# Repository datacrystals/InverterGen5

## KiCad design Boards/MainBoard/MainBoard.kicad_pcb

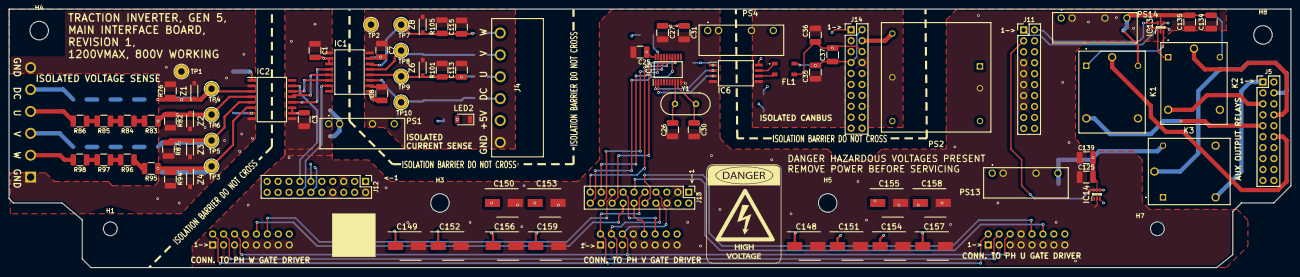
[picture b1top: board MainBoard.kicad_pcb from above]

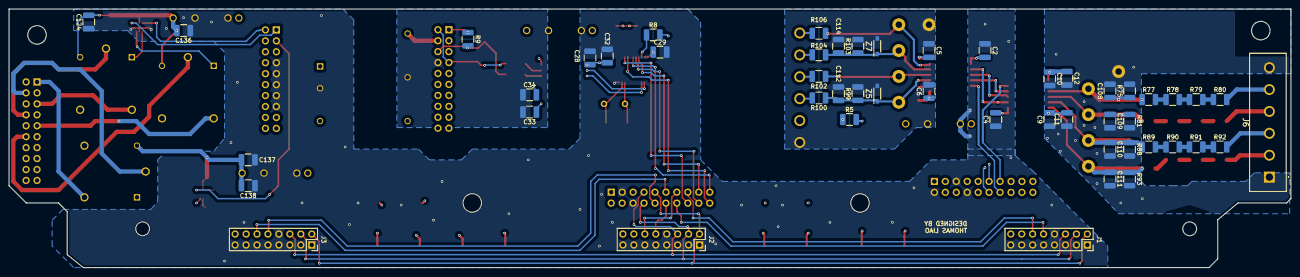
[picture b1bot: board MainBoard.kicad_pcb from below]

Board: 6 copper layers, 297.5 x 60.0 mm, 139 parts (50 on the bottom side), 85 nets.

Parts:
C1, C3, C5, C6, C9, C10, C25, C31, C32, C34: 100nF; C_1210_3225Metric_Pad1.33x2.70mm_HandSolder
C2, C4, C7, C8, C11, C12: 1uF; C_1210_3225Metric_Pad1.33x2.70mm_HandSolder
C26, C30, C35, C36, C37: 22pF; C_1210_3225Metric_Pad1.33x2.70mm_HandSolder
C27, C28, C29, C33, C124, C125, C134, C135, C136, C137, C138, C139: 10uF; C_1210_3225Metric_Pad1.33x2.70mm_HandSolder
C108, C109, C110, C111, C112, C113, C114, C115: 10nF; C_1210_3225Metric_Pad1.33x2.70mm_HandSolder
C148, C149, C150, C151, C152, C153, C154, C155, C156, C157, C158, C159: UCM1H101MCL1GS; CAPAE660X800N
FL1: ACT45B-101-2P-TL003; ACT45B1012PTL003
H1, H7: MountingHole; MountingHole_3.2mm_M3
H3, H4, H5, H8: MountingHole; MountingHole_4.3mm_M4
IC1, IC2: MAX22530AWE+; SOIC127P1032X265-16N
IC5: MCP2515-e_ST; SOP65P640X120-20N
IC6: ISO1042BDWVR; SOIC127P1150X280-8N
IC13, IC14: DRDNB21D-7; SOT65P210X110-6N
J1, J2, J3: Conn_02x08_Counter_Clockwise; PinSocket_2x08_P2.54mm_Vertical
J4: TBP01R1-508-06BE; TBP01R150806BE
J5, J11, J12, J13, J14: Conn_02x10_Counter_Clockwise; PinHeader_2x10_P2.54mm_Vertical
J6: TBP01R2-508-06BE; TBP01R250806BE
K1, K2, K3: AWHSH105D00G
LED2: LTST-C230CKT; LEDC3216X120N
PS1, PS4, PS13, PS14: RKE-1205S_H; RKE1205SH
PS2: REC10K-2424DAW_H2; REC10K-AW
R5, R76, R82, R88, R94, R99, R101, R103, R105: 1k; R_1210_3225Metric_Pad1.30x2.65mm_HandSolder
R8: 4.7k; R_1210_3225Metric_Pad1.30x2.65mm_HandSolder
R9: 120; R_1210_3225Metric_Pad1.30x2.65mm_HandSolder
R75, R81, R87, R93: 2k; R_1210_3225Metric_Pad1.30x2.65mm_HandSolder
R77, R78, R79, R80, R83, R84, R85, R86, R89, R90, R91, R92, R95, R96, R97, R98: 250k; R_1210_3225Metric_Pad1.30x2.65mm_HandSolder
R100, R102, R104, R106: 5k; R_1210_3225Metric_Pad1.30x2.65mm_HandSolder
TP1, TP2, TP3, TP4, TP5, TP6, TP7, TP8, TP9, TP10: TestPoint; TestPoint_Loop_D2.54mm_Drill1.5mm_Beaded
Y1: 8MHz; Crystal_HC49-4H_Vertical
Z1, Z2, Z3, Z4, Z5, Z6, Z7, Z8: SZMMSZ4678T1G; SOD3716X135N

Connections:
/+3.3V_A: C1.2, C2.2, C3.2, C4.2, C25.1, C28.2, C29.1, C32.1, C148.1 (+), C149.1 (+), C150.1 (+), C151.1 (+), IC1.10 (VDDPL), IC1.11 (VDDL), IC2.10 (VDDPL), IC2.11 (VDDL), IC5.20 (VDD), IC6.1 (VCC1), J1.14, J2.14, J3.14, J12.1, J12.4, J12.7, J13.1, J13.4, R8.2
/+5V_Y: J4.5, PS1.7 (+VOUT), R5.2
/+12V_A: C27.1, C31.1, C152.1 (+), C153.1 (+), C154.1 (+), C155.1 (+), C156.1 (+), C157.1 (+), C158.1 (+), C159.1 (+), J1.16, J2.16, J3.16, J11.6, J11.8, J11.10, J11.12, J11.14, J12.3, J12.6, J12.9, J13.2, J13.5, PS1.1 (+VIN), PS2.1 (+VIN), PS4.1 (+VIN), PS13.1 (+VIN), PS14.1 (+VIN)
/ADC_1/ADC2_5VFILTER_1/OUT: C112.1, IC1.3 (AIN1), R99.1, R100.1, TP10.1, Z5.1 (K)
/ADC_1/ADC2_5VFILTER_2/OUT: C113.1, IC1.4 (AIN2), R101.1, R102.1, TP9.1, Z6.1 (K)
/ADC_1/ADC2_5VFILTER_3/OUT: C114.1, IC1.5 (AIN3), R103.1, R104.1, TP8.1, Z7.1 (K)
/ADC_1/ADC2_5VFILTER_4/OUT: C115.1, IC1.6 (AIN4), R105.1, R106.1, TP7.1, Z8.1 (K)
/ADC_1/VoltageSenseInputStage1/LV_OUT: C109.1, IC2.4 (AIN2), R81.1, R82.1, R83.1, TP6.1, Z2.1 (K)
/ADC_1/VoltageSenseInputStage2/LV_OUT: C110.1, IC2.5 (AIN3), R87.1, R88.1, R89.1, TP5.1, Z3.1 (K)
/ADC_1/VoltageSenseInputStage3/LV_OUT: C111.1, IC2.6 (AIN4), R93.1, R94.1, R95.1, TP3.1, Z4.1 (K)
/ADC_1/VoltageSenseInputStage/LV_OUT: C108.1, IC2.3 (AIN1), R75.1, R76.1, R77.1, TP4.1, Z1.1 (K)
/CAN_5V_OUT: C33.1, C34.2, IC6.8 (VCC2), PS4.7 (+VOUT)
/CAN_24V_OUT: J14.4, PS2.6 (+VOUT)
/CAN_GND: C33.2, C34.1, C35.1, C36.2, IC6.5 (GND2), J14.8, PS2.5 (COM), PS4.5 (-VOUT)
/CAN_HIGH: C35.2, C37.1, FL1.4, J14.2, J14.7
/CAN_JUMPER_B: J14.1, R9.1
/CAN_LOW: C36.1, C37.2, FL1.3, J14.6, R9.2
/DC_LINK_VSENSE_U: J6.5, R80.2
/FAULT: J1.2, J2.2, J3.2, J13.9
/GND_A: C1.1, C2.1, C3.1, C4.1, C25.2, C26.2, C27.2, C28.1, C29.2, C30.2, C31.2, C32.2, C124.1, C125.1, C134.1, C135.1, C136.1, C137.1, C138.1, C139.1, C148.2 (-), C149.2 (-), C150.2 (-), C151.2 (-), C152.2 (-), C153.2 (-), C154.2 (-), C155.2 (-), C156.2 (-), C157.2 (-), C158.2 (-), C159.2 (-), IC1.9 (GNDL), IC2.9 (GNDL), IC5.10 (VSS), IC6.4 (GND1), IC13.2 (E1/E2), IC14.2 (E1/E2), IC14.6 (B1), J1.1, J1.3, J1.5, J1.7, J1.8, J1.9, J1.11, J1.13, J1.15, J2.1, J2.3, J2.5, J2.7, J2.8, J2.9, J2.11, J2.13, J2.15, J3.1, J3.3, J3.5, J3.7, J3.8, J3.9, J3.11, J3.13, J3.15, J11.7, J11.9, J11.11, J11.13, J11.15, J12.2, J12.5, J12.8, J13.3, J13.6, PS1.2 (-VIN), PS2.2 (-VIN), PS4.2 (-VIN), PS13.2 (-VIN), PS13.5 (-VOUT), PS14.2 (-VIN), PS14.5 (-VOUT)
/GND_U: C9.1, C10.2, C11.1, C12.2, C108.2, C109.2, C110.2, C111.2, IC2.2 (AGND), IC2.8 (GNDF), J6.1, J6.6, R75.2, R76.2, R81.2, R82.2, R87.2, R88.2, R93.2, R94.2, TP1.1, Z1.2 (A), Z2.2 (A), Z3.2 (A), Z4.2 (A)
/ISENSE_DC_LINK_Y: J4.4, R100.2
/ISENSE_GND_Y: C5.1, C6.2, C7.1, C8.2, C112.2, C113.2, C114.2, C115.2, IC1.2 (AGND), IC1.8 (GNDF), J4.6, LED2.1 (K), PS1.5 (-VOUT), R99.2, R101.2, R103.2, R105.2, TP2.1, Z5.2 (A), Z6.2 (A), Z7.2 (A), Z8.2 (A)
/ISENSE_PH_U_Y: J4.3, R102.2
/ISENSE_PH_V_Y: J4.2, R104.2
/ISENSE_PH_W_Y: J4.1, R106.2
/OutputRelays/+5V_A_INT: C125.2, C137.2, C138.2, C139.2, IC14.5 (K1/K2), K3.4 (COIL_2), PS13.7 (+VOUT)
/OutputRelays/+5V_A_INT_2: C124.2, C134.2, C135.2, C136.2, IC13.5 (K1/K2), K1.4 (COIL_2), K2.4 (COIL_2), PS14.7 (+VOUT)
/PH_U_H: J1.12, J13.15
/PH_U_L: J1.10, J13.14
/PH_U_VSENSE_U: J6.4, R86.2
/PH_V_H: J2.12, J13.13
/PH_V_L: J2.10, J13.12
/PH_V_VSENSE_U: J6.3, R92.2
/PH_W_H: J3.12, J13.11
/PH_W_L: J3.10, J13.10
/PH_W_VSENSE_U: J6.2, R98.2
/READY: J1.4, J2.4, J3.4, J13.8
/RELAY1_COM: J5.12, K1.5 (COM)
/RELAY1_NO: J5.9, K1.2 (NO)
/RELAY2_COM: J5.8, K2.5 (COM)
/RELAY2_NO: J5.5, K2.2 (NO)
/RELAY3_COM: J5.4, K3.5 (COM)
/RELAY3_NO: J5.1, K3.2 (NO)
/RELAY_1_A: IC13.4 (B2), J11.1
/RELAY_2_A: IC13.6 (B1), J11.2
/RELAY_3_A: IC14.4 (B2), J11.3
/RESET: J1.6, J2.6, J3.6, J13.7
/SPI1_CAN_CS_A: IC5.18 (~CS), J13.17
/SPI1_CAN_INT_A: IC5.13 (~INT), J13.16
/SPI1_RX_A: IC5.17 (SO), J13.18
/SPI1_SCK_A: IC5.14 (SCK), J13.20
/SPI1_TX_A: IC5.16 (SI), J13.19
/SPI2_ADC1_CS_A: IC2.15 (~CS), J12.13
/SPI2_ADC2_CS_A: IC1.15 (~CS), J12.14
/SPI2_RX_A: IC1.12 (SDO), IC2.12 (SDO), J12.10
/SPI2_SCK_A: IC1.14 (SCLK), IC2.14 (SCLK), J12.12
/SPI2_TX_A: IC1.13 (SDI), IC2.13 (SDI), J12.11
unnamed: C6.1, C8.1, IC1.1 (REF)
unnamed: C5.2, C7.2, IC1.7 (VDDF)
unnamed: C10.1, C12.1, IC2.1 (REF)
unnamed: C9.2, C11.2, IC2.7 (VDDF)
unnamed: C30.1, IC5.9 (OSC1), Y1.2
unnamed: C26.1, IC5.8 (OSC2), Y1.1
unnamed: IC5.2 (RXCAN), IC6.3 (RXD)
unnamed: IC5.1 (TXCAN), IC6.2 (TXD)
unnamed: IC5.19 (~RESET), R8.1
unnamed: FL1.1, IC6.7 (CANH)
unnamed: FL1.2, IC6.6 (CANL)
unnamed: IC13.1 (C1/A1), K2.1 (COIL_1)
unnamed: IC13.3 (C2/A2), K1.1 (COIL_1)
unnamed: IC14.3 (C2/A2), K3.1 (COIL_1)
unnamed: LED2.2 (A), R5.1
unnamed: R77.2, R78.1
unnamed: R78.2, R79.1
unnamed: R79.2, R80.1
unnamed: R83.2, R84.1
unnamed: R84.2, R85.1
unnamed: R85.2, R86.1
unnamed: R89.2, R90.1
unnamed: R90.2, R91.1
unnamed: R91.2, R92.1
unnamed: R95.2, R96.1
unnamed: R96.2, R97.1
unnamed: R97.2, R98.1

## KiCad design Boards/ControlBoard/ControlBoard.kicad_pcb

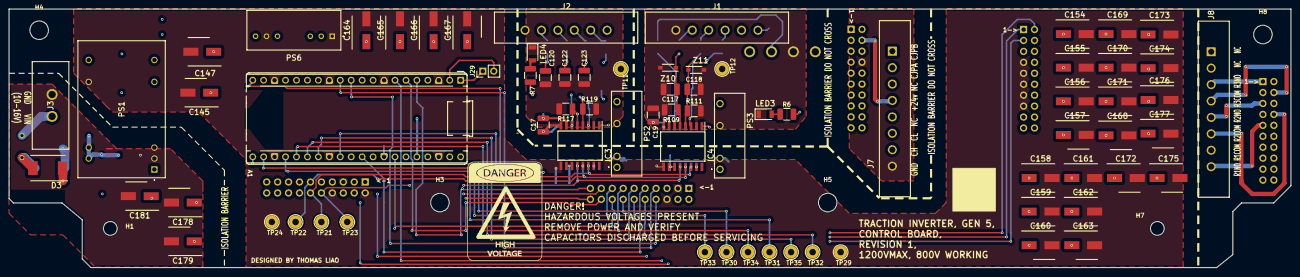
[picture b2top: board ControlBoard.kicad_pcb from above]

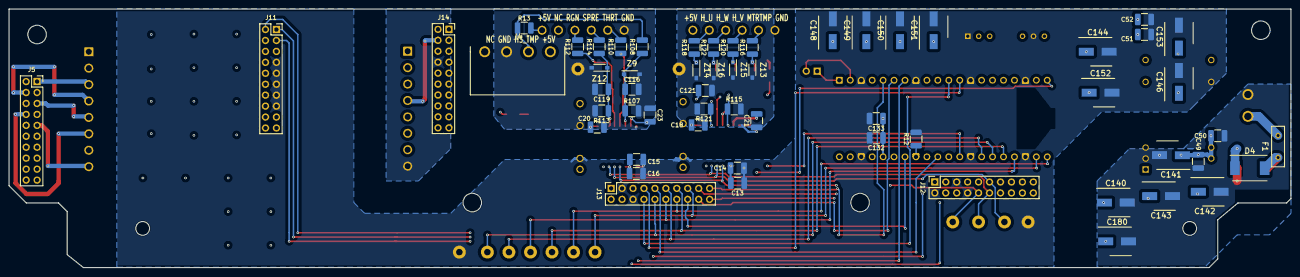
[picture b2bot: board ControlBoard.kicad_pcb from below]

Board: 6 copper layers, 297.5 x 60.0 mm, 137 parts (58 on the bottom side), 72 nets.

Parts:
A1: RaspberryPi_Pico; RaspberryPi_Pico_Common_THT
C13, C14, C17, C18, C19, C20, C50, C52, C132: 100nF; C_1210_3225Metric_Pad1.33x2.70mm_HandSolder
C15, C16, C21, C23, C49, C51: 1uF; C_1210_3225Metric_Pad1.33x2.70mm_HandSolder
C116, C117, C118, C119, C120, C121, C122, C123: 10nF; C_1210_3225Metric_Pad1.33x2.70mm_HandSolder
C133: 10uF; C_1210_3225Metric_Pad1.33x2.70mm_HandSolder
C140, C141, C142, C143, C144, C145, C146, C147, C148, C149, C150, C151, C152, C153, C154, C155, C156, C157, C158, C159, C160, C161, C162, C163, C164, C165, C166, C167, C168, C169, C170, C171, C172, C173, C174, C175, C176, C177, C178, C179, C180, C181: UCM1H101MCL1GS; CAPAE660X800N
D3, D4: S3N; DIOM8059X265N
F1: MF-RHT200_32-2; MFRHT200322
H1, H7: MountingHole; MountingHole_3.2mm_M3
H3, H4, H5, H8: MountingHole; MountingHole_4.3mm_M4
IC3, IC4: MAX22530AWE+; SOIC127P1032X265-16N
J1, J2: TBP02R2W-381-06BE; TBP02R2W38106BE
J3: TBP01R2W-508-02BE; TBP01R2W50802BE
J4: TBP01R1-508-04BE; TBP01R150804BE
J5, J11, J12, J13, J14: Conn_02x10_Counter_Clockwise; PinSocket_2x10_P2.54mm_Vertical
J7, J8: TBP02R2W-381-08BE; TBP02R2W38108BE
J29: Conn_01x02_Pin; PinHeader_1x02_P2.54mm_Vertical
LED3, LED4: LTST-C230CKT; LEDC3216X120N
PS1: SCW20A-12; SCW20A12
PS2, PS3: RKE-1205S_H; RKE1205SH
PS6: RD7-12S033R; RD712S033R
R6, R7, R107, R109, R111, R113, R115, R117, R119, R121: 1k; R_1210_3225Metric_Pad1.30x2.65mm_HandSolder
R12: 0; R_1210_3225Metric_Pad1.30x2.65mm_HandSolder
R13: 10k; R_1210_3225Metric_Pad1.30x2.65mm_HandSolder
R108, R110, R112, R114, R116, R118, R120, R122: 5k; R_1210_3225Metric_Pad1.30x2.65mm_HandSolder
TP11, TP12, TP21, TP22, TP23, TP24, TP29, TP30, TP31, TP32, TP33, TP34, TP35: TestPoint; TestPoint_Loop_D2.54mm_Drill1.5mm_Beaded
Z9, Z10, Z11, Z12, Z13, Z14, Z15, Z16: SZMMSZ4678T1G; SOD3716X135N

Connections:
/+3.3V_A: A1.36 (3V3), C13.2, C14.2, C15.2, C16.2, C132.1, C133.1, C148.1 (+), C149.1 (+), C150.1 (+), C151.1 (+), C154.1 (+), C155.1 (+), C156.1 (+), C157.1 (+), C164.1 (+), C165.1 (+), C166.1 (+), C167.1 (+), C168.1 (+), C169.1 (+), C170.1 (+), C171.1 (+), IC3.10 (VDDPL), IC3.11 (VDDL), IC4.10 (VDDPL), IC4.11 (VDDL), J12.1, J12.4, J12.7, J13.1, J13.4, PS6.6 (+VOUT)
/+5V_V: J1.6, J4.1, PS3.7 (+VOUT), R6.2, R13.2
/+5V_W: J2.6, PS2.7 (+VOUT), R7.2
/+12V_A: C51.2, C52.2, C144.1 (+), C145.1 (+), C146.1 (+), C147.1 (+), C152.1 (+), C153.1 (+), C158.1 (+), C159.1 (+), C160.1 (+), C161.1 (+), C162.1 (+), C163.1 (+), C172.1 (+), C173.1 (+), C174.1 (+), C175.1 (+), C176.1 (+), C177.1 (+), J11.6, J11.8, J11.10, J11.12, J11.14, J12.3, J12.6, J12.9, J13.2, J13.5, PS1.14 (+VOUT), PS2.1 (+VIN), PS3.1 (+VIN), PS6.2 (+VIN)
/ADC_2/ADC3_5VFILTER_1/OUT: C120.1, IC3.6 (AIN4), R115.1, R116.1, Z13.1 (K)
/ADC_2/ADC3_5VFILTER_2/OUT: C121.1, IC3.5 (AIN3), R117.1, R118.1, Z14.1 (K)
/ADC_2/ADC3_5VFILTER_3/OUT: C122.1, IC3.4 (AIN2), R119.1, R120.1, Z15.1 (K)
/ADC_2/ADC3_5VFILTER_4/OUT: C123.1, IC3.3 (AIN1), R121.1, R122.1, Z16.1 (K)
/ADC_2/ADC4_5VFILTER_1/OUT: C116.1, IC4.6 (AIN4), R107.1, R108.1, Z9.1 (K)
/ADC_2/ADC4_5VFILTER_2/OUT: C117.1, IC4.5 (AIN3), R109.1, R110.1, Z10.1 (K)
/ADC_2/ADC4_5VFILTER_3/OUT: C118.1, IC4.4 (AIN2), R111.1, R112.1, Z11.1 (K)
/ADC_2/ADC4_5VFILTER_4/OUT: C119.1, IC4.3 (AIN1), R113.1, R114.1, Z12.1 (K)
/CAN_24V_OUT: J7.4, J14.4
/CAN_GND: J7.8, J14.8
/CAN_HIGH: J7.7, J14.7
/CAN_JUMPER_A: J7.2, J14.2
/CAN_JUMPER_B: J7.1, J14.1
/CAN_LOW: J7.6, J14.6
/FAULT: A1.31 (GPIO26_ADC0), J13.9
/GND_A: A1.3 (GND), A1.8 (GND), A1.13 (GND), A1.18 (GND), A1.23 (GND), A1.28 (GND), A1.38 (GND), C13.1, C14.1, C15.1, C16.1, C51.1, C52.1, C132.2, C133.2, C144.2 (-), C145.2 (-), C146.2 (-), C147.2 (-), C148.2 (-), C149.2 (-), C150.2 (-), C151.2 (-), C152.2 (-), C153.2 (-), C154.2 (-), C155.2 (-), C156.2 (-), C157.2 (-), C158.2 (-), C159.2 (-), C160.2 (-), C161.2 (-), C162.2 (-), C163.2 (-), C164.2 (-), C165.2 (-), C166.2 (-), C167.2 (-), C168.2 (-), C169.2 (-), C170.2 (-), C171.2 (-), C172.2 (-), C173.2 (-), C174.2 (-), C175.2 (-), C176.2 (-), C177.2 (-), IC3.9 (GNDL), IC4.9 (GNDL), J11.7, J11.9, J11.11, J11.13, J11.15, J12.2, J12.5, J12.8, J13.3, J13.6, PS1.16 (-VOUT), PS2.2 (-VIN), PS3.2 (-VIN), PS6.1 (-VIN), PS6.7 (-VOUT), R12.2, TP24.1, TP29.1
/GND_V: C19.1, C20.2, C23.1, C116.2, C117.2, C118.2, C119.2, IC4.2 (AGND), IC4.8 (GNDF), J1.1, J4.3, LED3.1 (K), PS3.5 (-VOUT), R107.2, R109.2, R111.2, R113.2, TP12.1, Z9.2 (A), Z10.2 (A), Z11.2 (A), Z12.2 (A)
/GND_W: C17.1, C18.2, C21.1, C120.2, C121.2, C122.2, C123.2, IC3.2 (AGND), IC3.8 (GNDF), J2.1, LED4.1 (K), PS2.5 (-VOUT), R115.2, R117.2, R119.2, R121.2, TP11.1, Z13.2 (A), Z14.2 (A), Z15.2 (A), Z16.2 (A)
/HALL_PH_U_W: J2.5, R118.2
/HALL_PH_V_W: J2.3, R120.2
/HALL_PH_W_W: J2.4, R122.2
/HEATSINK_TMP_V: J4.2, R13.1, R108.2
/MTR_TMP_W: J2.2, R116.2
/PH_U_H: A1.22 (GPIO17), J13.15, TP33.1
/PH_U_L: A1.21 (GPIO16), J13.14, TP30.1
/PH_V_H: A1.25 (GPIO19), J13.13, TP34.1
/PH_V_L: A1.24 (GPIO18), J13.12, TP31.1
/PH_W_H: A1.27 (GPIO21), J13.11, TP35.1
/PH_W_L: A1.26 (GPIO20), J13.10, TP32.1
/Power/GND_Z: C49.1, C50.1, C140.2 (-), C141.2 (-), C142.2 (-), C143.2 (-), C178.2 (-), C179.2 (-), C180.2 (-), C181.2 (-), J3.2, PS1.2 (-VIN_1), PS1.3 (-VIN_2)
/Power/VIN_FUSED_Z: C49.2, C50.2, C140.1 (+), C141.1 (+), C142.1 (+), C143.1 (+), C178.1 (+), C179.1 (+), C180.1 (+), C181.1 (+), D3.1 (K), D4.1 (K), PS1.22 (+VIN_1), PS1.23 (+VIN_2)
/Power/VIN_Z: F1.1, J3.1
/READY: A1.11 (GPIO8), J13.8
/REGEN_THROTTLE_V: J1.4, R112.2
/RELAY1_COM: J5.12, J8.7
/RELAY1_NO: J5.9, J8.8
/RELAY2_COM: J5.8, J8.6
/RELAY2_NO: J5.5, J8.5
/RELAY3_COM: J5.4, J8.4
/RELAY3_NO: J5.1, J8.3
/RELAY_1_A: A1.7 (GPIO5), J11.1
/RELAY_2_A: A1.9 (GPIO6), J11.2
/RELAY_3_A: A1.10 (GPIO7), J11.3
/RESET: A1.12 (GPIO9), J13.7
/SPARE_V: J1.3, R114.2
/SPI1_CAN_CS_A: A1.32 (GPIO27_ADC1), J13.17
/SPI1_CAN_INT_A: A1.34 (GPIO28_ADC2), J13.16
/SPI1_RX_A: A1.6 (GPIO4), J13.18
/SPI1_SCK_A: A1.4 (GPIO2), J13.20
/SPI1_TX_A: A1.5 (GPIO3), J13.19
/SPI2_ADC1_CS_A: A1.17 (GPIO13), J12.13
/SPI2_ADC2_CS_A: A1.19 (GPIO14), J12.14
/SPI2_ADC3_CS_A: A1.20 (GPIO15), IC3.15 (~CS)
/SPI2_ADC4_CS_A: A1.29 (GPIO22), IC4.15 (~CS)
/SPI2_RX_A: A1.16 (GPIO12), IC3.12 (SDO), IC4.12 (SDO), J12.10, TP23.1
/SPI2_SCK_A: A1.14 (GPIO10), IC3.14 (SCLK), IC4.14 (SCLK), J12.12, TP21.1
/SPI2_TX_A: A1.15 (GPIO11), IC3.13 (SDI), IC4.13 (SDI), J12.11, TP22.1
/THROTTLE_V: J1.2, R110.2
unnamed: A1.33 (AGND), R12.1
unnamed: A1.1 (GPIO0), J29.1
unnamed: A1.2 (GPIO1), J29.2
unnamed: D3.2 (A), D4.2 (A), F1.2
unnamed: C18.1, IC3.1 (REF)
unnamed: C17.2, C21.2, IC3.7 (VDDF)
unnamed: C20.1, IC4.1 (REF)
unnamed: C19.2, C23.2, IC4.7 (VDDF)
unnamed: LED3.2 (A), R6.1
unnamed: LED4.2 (A), R7.1

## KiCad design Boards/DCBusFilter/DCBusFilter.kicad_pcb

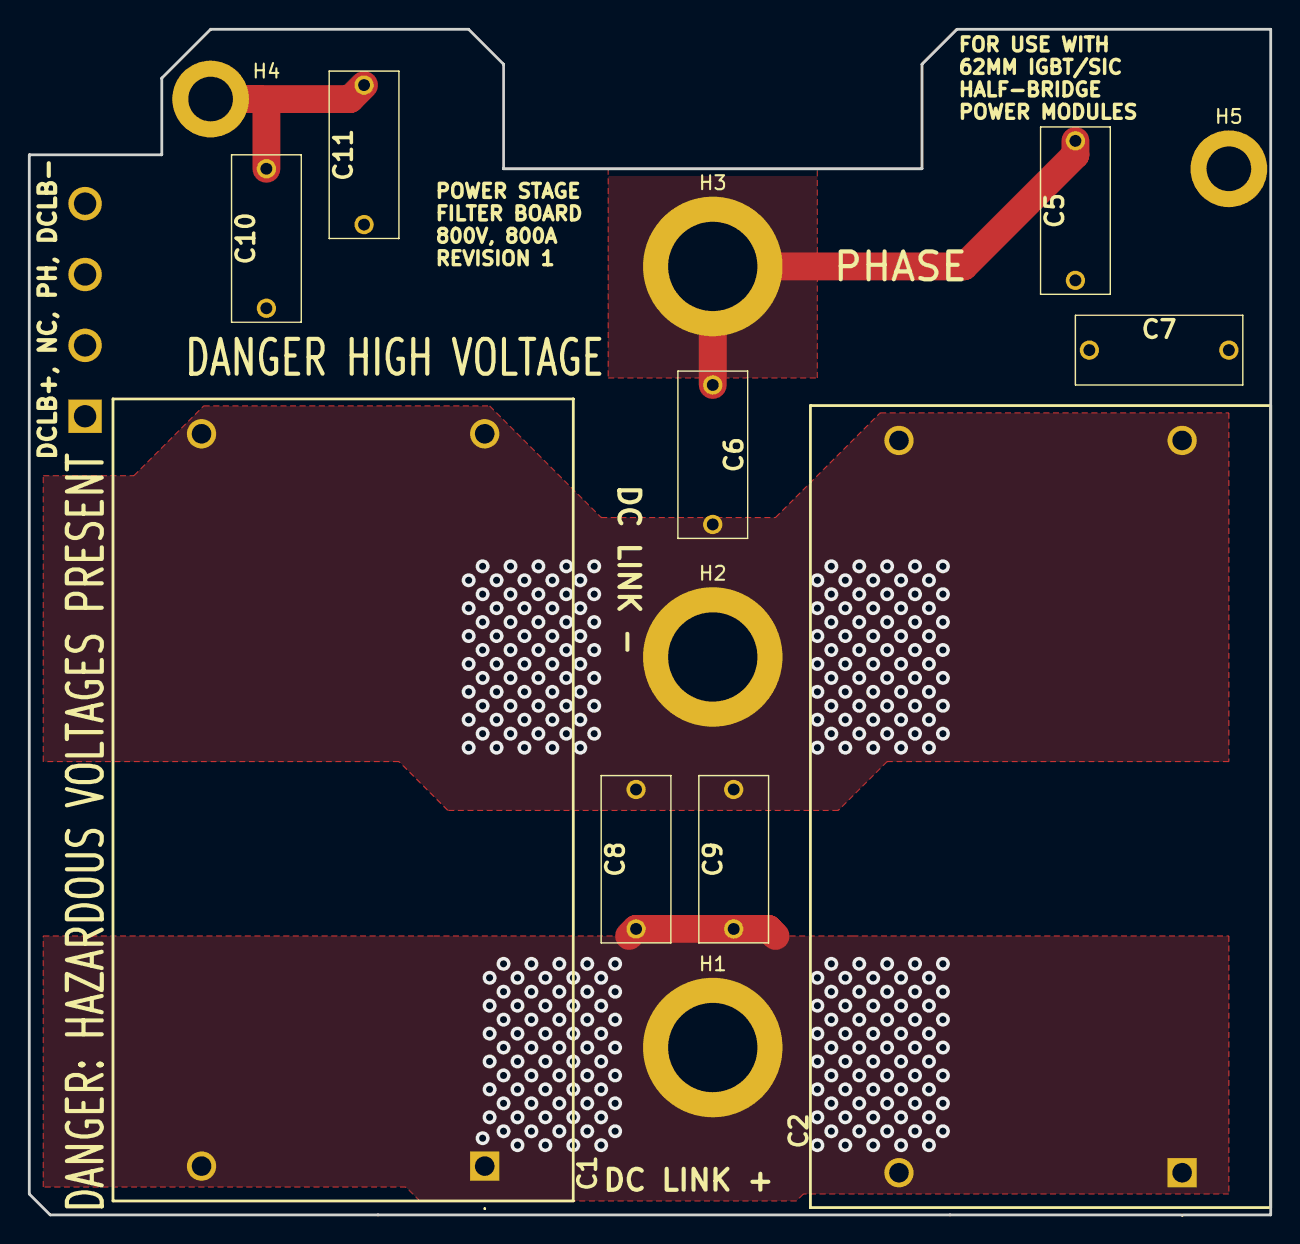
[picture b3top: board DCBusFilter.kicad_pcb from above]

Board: 4 copper layers, 89.0 x 85.0 mm, 15 parts (1 on the bottom side), 5 nets.

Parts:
C1, C2: MKP1848S61010JY5B
C5, C6, C7, C8, C9, C10, C11: VY1222M47Y5UQ6TV0
H1, H2, H3: MountingHole_Pad; MountingHole_6.4mm_M6_ISO14580_Pad
H4, H5: MountingHole_Pad; MountingHole_3.2mm_M3_ISO14580_Pad
J1: TBP01R2-508-04BE; SHDR4W100P0X508_1X4_2192X850X1200P

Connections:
/CHASSIS_GND: C10.1, C11.1, H4.1
/CHASSIS_GND_1: C7.1, H5.1
/DC_LINK_+: C1.1, C1.3, C2.1, C2.3, C5.2, C7.2, C8.2, C9.2, H1.1, J1.1
/DC_LINK_-: C1.2, C1.4, C2.2, C2.4, C6.1, C8.1, C9.1, C10.2, H2.1, J1.4
/PHASE_LEG: C5.1, C6.2, C11.2, H3.1, J1.3

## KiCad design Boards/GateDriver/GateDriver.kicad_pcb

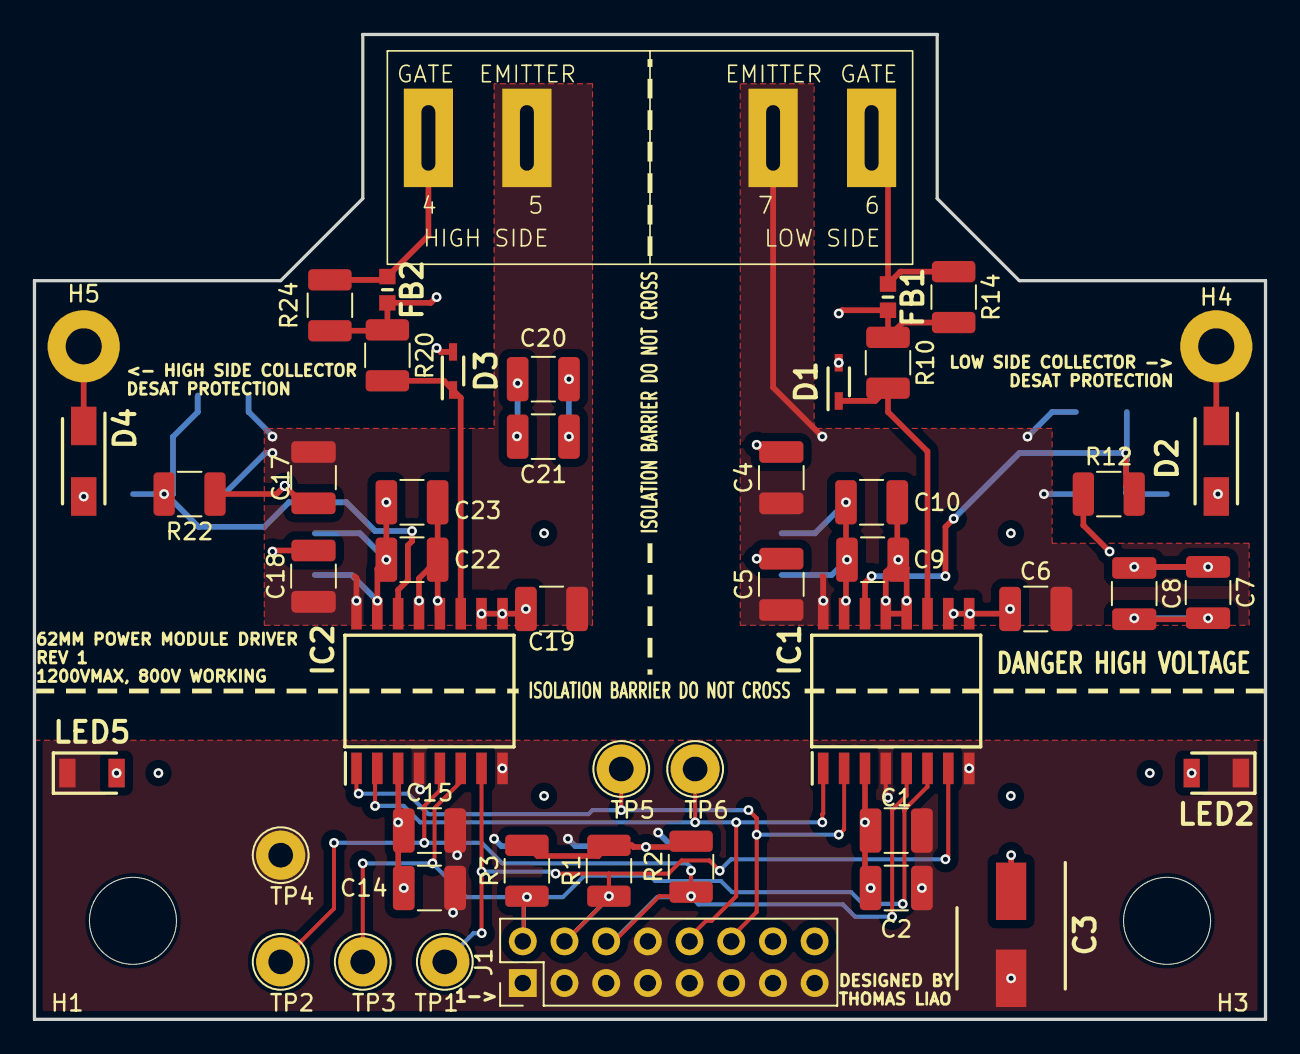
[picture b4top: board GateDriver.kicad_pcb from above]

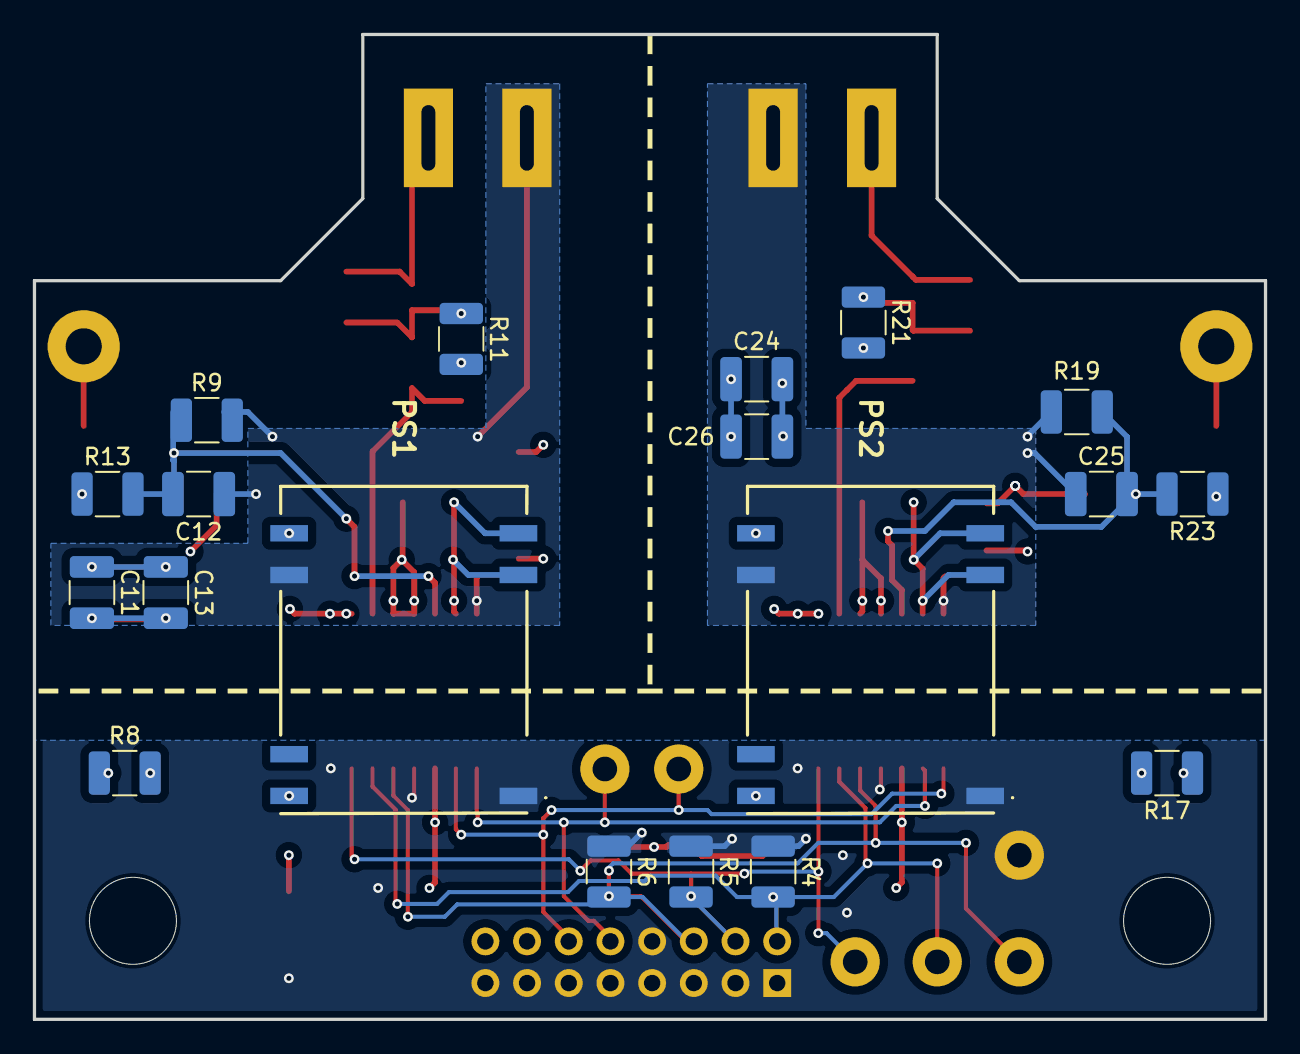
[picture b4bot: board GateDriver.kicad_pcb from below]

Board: 6 copper layers, 75.0 x 60.0 mm, 69 parts (19 on the bottom side), 30 nets.

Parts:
C1, C5, C6, C9, C12, C14, C18, C19, C22, C25: 100nF; C_1210_3225Metric_Pad1.33x2.70mm_HandSolder
C2, C4, C7, C8, C10, C11, C13, C15, C17, C20, C21, C23, C24, C26: 10uF; C_1210_3225Metric_Pad1.33x2.70mm_HandSolder
C3: UCM1H101MCL1GS; CAPAE660X800N
D1, D3: BAT54WS-7-F; SOD2513X120N
D2, D4: FM2000GP-TP; DIOM5226X244N
FB1, FB2: FBMJ1608HS220NTR; BEADC1608X100N
H1, H3: MountingHole; MountingHole_5.3mm_M5
H4, H5: MountingHole_Pad; MountingHole_2.2mm_M2_Pad
IC1, IC2: ADUM4136BRWZ; SOIC127P1032X265-16N
J1: Conn_02x08_Counter_Clockwise; PinHeader_2x08_P2.54mm_Vertical
LED2: LTST-C230CKT; LEDC3216X120N
LED5: LTST-C230GKT; LEDC3216X120N
PS1, PS2: MGJ2D121509MPC-R7; MGJ2D121509MPCR7
Q1: 62mm_power_module
R1, R2, R3, R4, R5, R6, R17: 4.7k; R_1210_3225Metric_Pad1.30x2.65mm_HandSolder
R8: 220; R_1210_3225Metric_Pad1.30x2.65mm_HandSolder
R9, R14, R19, R24: 0; R_1210_3225Metric_Pad1.30x2.65mm_HandSolder
R10, R20: 9.1; R_1210_3225Metric_Pad1.30x2.65mm_HandSolder
R11, R21: 6.8; R_1210_3225Metric_Pad1.30x2.65mm_HandSolder
R12, R13, R22, R23: 1k; R_1210_3225Metric_Pad1.30x2.65mm_HandSolder
TP1, TP2, TP3, TP4, TP5, TP6: TestPoint; TestPoint_Loop_D2.54mm_Drill1.5mm_Beaded

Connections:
/+3.3V_A: C1.2, C2.1, C14.2, C15.1, IC1.3 (VDD1), IC2.3 (VDD1), J1.14, R1.2, R2.2, R3.2, R8.2
/+12V_A: C3.1 (+), J1.16, PS1.8 (+VIN), PS2.8 (+VIN), R17.2
/FAULT: IC1.6 (~FAULT), IC2.6 (~FAULT), J1.2, R3.1, R4.2, TP3.1
/GND_A: C1.1, C2.2, C3.2 (-), C14.1, C15.2, IC1.4 (VSS1_1), IC1.8 (VSS1_2), IC2.4 (VSS1_1), IC2.8 (VSS1_2), J1.1, J1.3, J1.5, J1.7, J1.8, J1.9, J1.11, J1.13, J1.15, LED2.1 (K), LED5.1 (K), PS1.1 (-VIN), PS2.1 (-VIN), R4.1, R5.1, R6.1, TP4.1
/PH_H: IC1.2 (VI-), IC2.1 (VI+), J1.12, TP5.1
/PH_H_C: D4.1 (K), H5.1
/PH_H_G: FB2.1, Q1.3 (HIGH_GATE), R24.1
/PH_L: IC1.1 (VI+), IC2.2 (VI-), J1.10, TP6.1
/PH_L_C: D2.1 (K), H4.1
/PH_L_G: FB1.1, Q1.1 (LOW_GATE), R14.1
/READY: IC1.7 (READY), IC2.7 (READY), J1.4, R1.1, R5.2, TP1.1
/RESET: IC1.5 (~RESET), IC2.5 (~RESET), J1.6, R2.1, R6.2, TP2.1
/SingleChannelDriver1/+15V_B: C4.2, C5.2, C7.1, C8.1, C9.2, C10.1, C11.1, C13.1, IC1.12 (VDD2_1), IC1.13 (VDD2_2), PS1.5 (+VOUT), R12.1
/SingleChannelDriver1/-9V_B: C6.1, C7.2, C8.2, C9.1, C10.2, C11.2, C13.2, IC1.9 (VSS2_1), IC1.10 (VSS2_2), IC1.15 (VSS2_3), PS1.3 (-VOUT_1), PS1.4 (-VOUT_2)
/SingleChannelDriver1/GND_B: C4.1, C5.1, C6.2, C12.1, IC1.16 (GND2), PS1.6 (0V), Q1.2 (LOW_EMITTER), R9.2
/SingleChannelDriver/+15V_B: C17.2, C18.2, C20.1, C21.1, C22.2, C23.1, C24.1, C26.1, IC2.12 (VDD2_1), IC2.13 (VDD2_2), PS2.5 (+VOUT), R22.1
/SingleChannelDriver/-9V_B: C19.1, C20.2, C21.2, C22.1, C23.2, C24.2, C26.2, IC2.9 (VSS2_1), IC2.10 (VSS2_2), IC2.15 (VSS2_3), PS2.3 (-VOUT_1), PS2.4 (-VOUT_2)
/SingleChannelDriver/GND_B: C17.1, C18.1, C19.2, C25.1, IC2.16 (GND2), PS2.6 (0V), Q1.4 (HIGH_EMITTER), R19.2
unnamed: D1.2 (A), R11.2
unnamed: D1.1 (K), IC1.11 (VOUT), R10.2
unnamed: D2.2 (A), R13.1
unnamed: D3.2 (A), R21.2
unnamed: D3.1 (K), IC2.11 (VOUT), R20.2
unnamed: D4.2 (A), R23.1
unnamed: FB1.2, R10.1, R11.1, R14.2
unnamed: FB2.2, R20.1, R21.1, R24.2
unnamed: C12.2, IC1.14 (DESAT), R9.1, R12.2, R13.2
unnamed: C25.2, IC2.14 (DESAT), R19.1, R22.2, R23.2
unnamed: LED2.2 (A), R8.1
unnamed: LED5.2 (A), R17.1

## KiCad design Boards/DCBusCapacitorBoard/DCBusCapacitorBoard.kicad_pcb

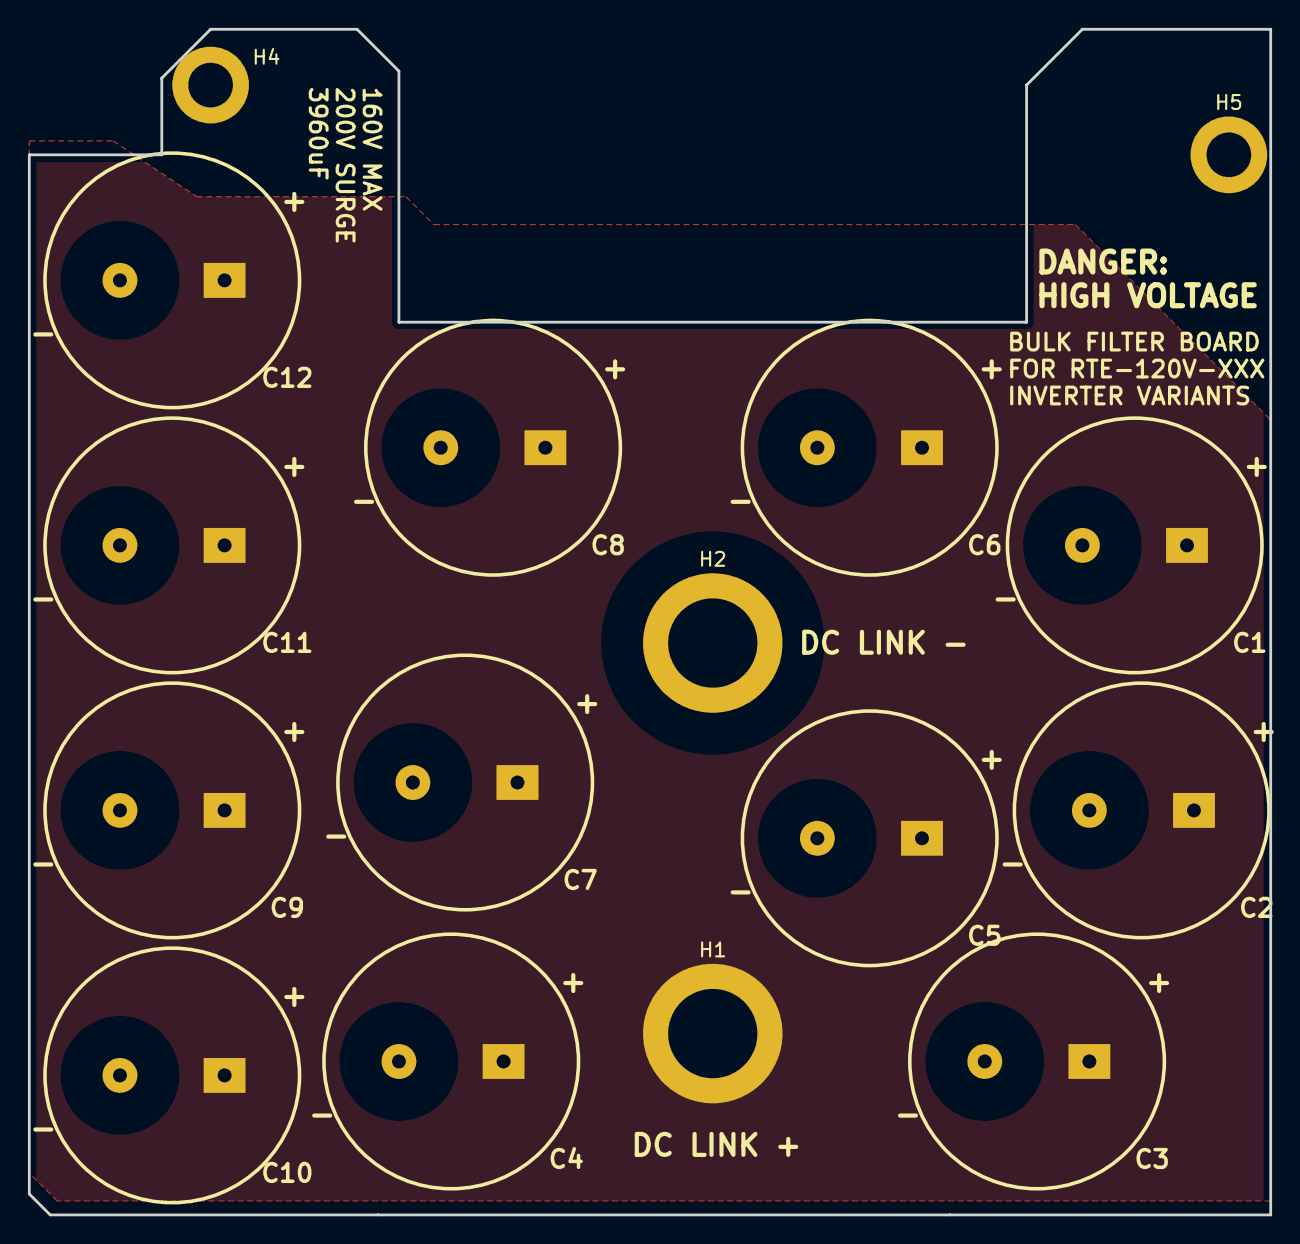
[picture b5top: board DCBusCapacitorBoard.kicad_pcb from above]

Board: 4 copper layers, 89.0 x 85.0 mm, 16 parts (0 on the bottom side), 2 nets, no tracks yet.

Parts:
C1, C2, C3, C4, C5, C6, C7, C8, C9, C10, C11, C12: UCS2C331MHD; CAPPRD750W80D1825H3200
H1, H2: MountingHole_Pad; MountingHole_6.4mm_M6_ISO14580_Pad
H4, H5: MountingHole_Pad; MountingHole_3.2mm_M3_ISO14580_Pad

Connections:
/DC_LINK_+: C1.1 (+), C2.1 (+), C3.1 (+), C4.1 (+), C5.1 (+), C6.1 (+), C7.1 (+), C8.1 (+), C9.1 (+), C10.1 (+), C11.1 (+), C12.1 (+), H1.1
/DC_LINK_-: C1.2 (-), C2.2 (-), C3.2 (-), C4.2 (-), C5.2 (-), C6.2 (-), C7.2 (-), C8.2 (-), C9.2 (-), C10.2 (-), C11.2 (-), C12.2 (-), H2.1

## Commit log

2026-01-24 layout control boards, add baseplate, refine mechanical layout
2026-01-25 Layout mainboard, add EMI filter caps
2026-01-25 Layout controlboard, update cad
2026-01-27 fix connector pinout
2026-01-31 add firmware beta
2026-01-31 add firmware todo
2026-02-01 fixed intellisense
2026-02-01 broken max2253x
2026-02-01 add flash command
2026-02-01 switch to 5mbit spi
2026-02-01 working vsense, gate drive
2026-02-02 multicore wip
2026-02-02 add hardware rcfm
2026-02-04 update for zero 75-10 pmsm motor
2026-02-04 fix encoder calibration
2026-02-04 added standoffs and screws
2026-02-05 added m4 holes
2026-02-05 added m3 holes
2026-02-05 extend busbar
2026-02-05 cleaned a bit, untested
2026-02-05 good encoder tracking
2026-02-05 working current
2026-02-05 async cmd
2026-02-05 refractor command system
2026-02-06 add new caps board
2026-02-06 Add Clearance To Main/CtrlBd, Increase main DCDC to 20w
2026-02-06 Add Clearance To DCLinkISense
